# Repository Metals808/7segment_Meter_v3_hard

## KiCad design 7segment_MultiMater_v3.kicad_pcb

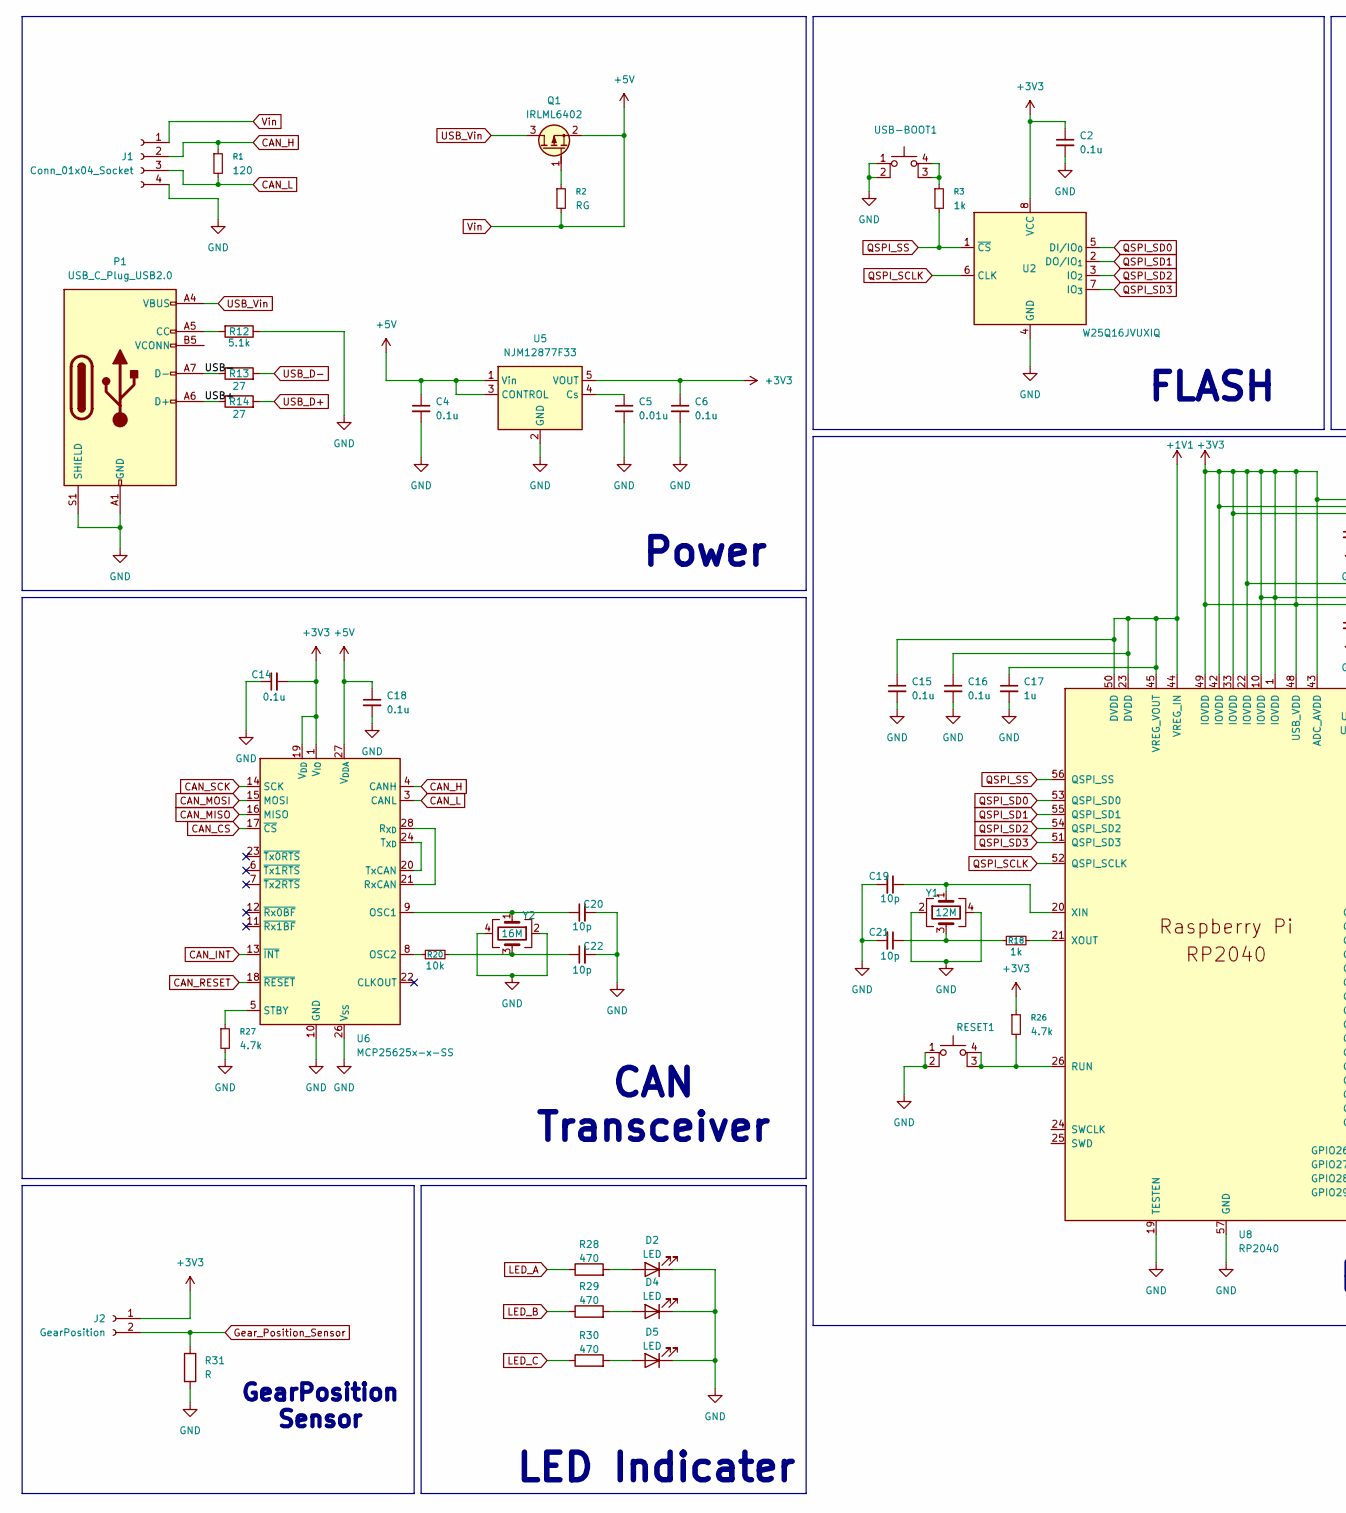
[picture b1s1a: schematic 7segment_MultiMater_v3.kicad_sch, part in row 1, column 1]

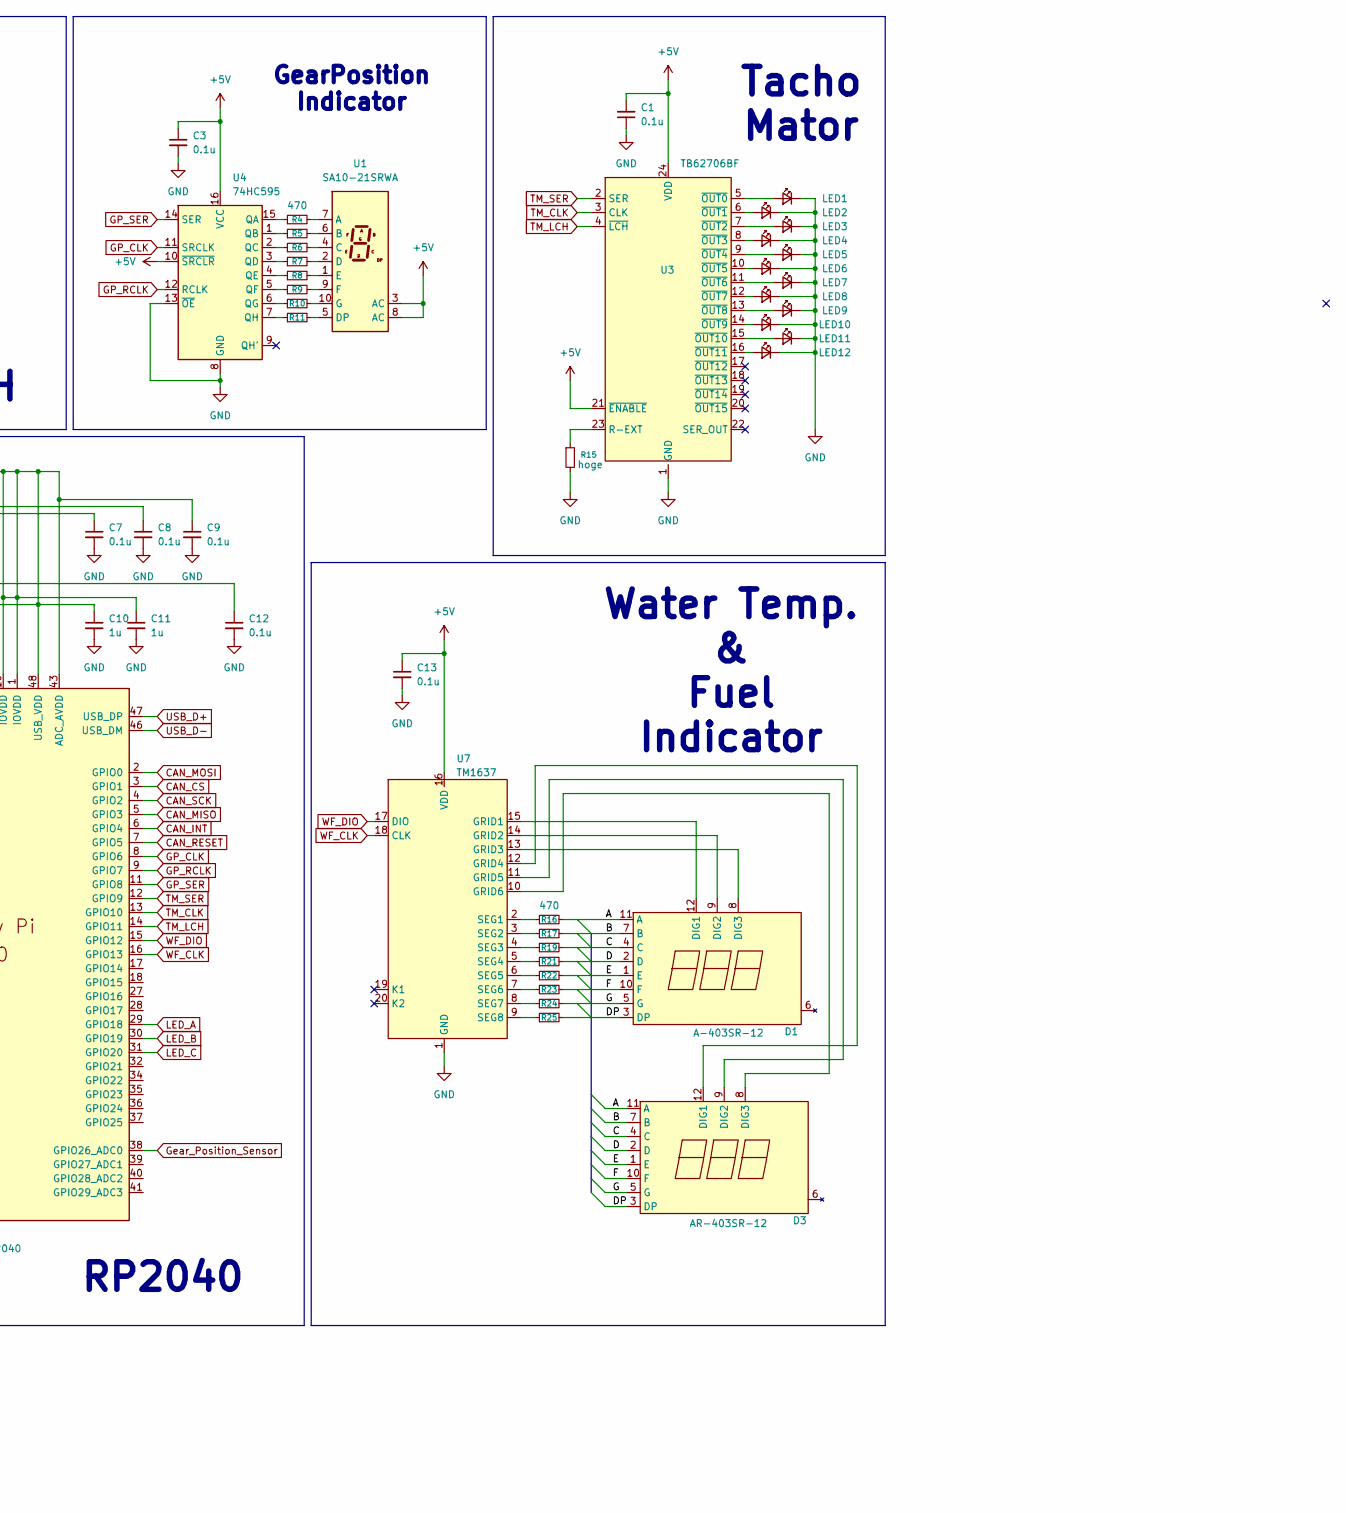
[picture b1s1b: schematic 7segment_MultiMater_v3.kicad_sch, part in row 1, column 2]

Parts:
C1, C2, C3, C4, C6, C7, C8, C9, C12, C13, C14, C15, C16, C18: 0.1u; C_0402_1005Metric
C5: 0.01u; C_0402_1005Metric
C10, C11, C17: 1u; C_0402_1005Metric
C19, C20, C21, C22: 10p; C_0402_1005Metric
D1: A-403SR-12; A403SR-12
D2, D4, D5: LED; LED_0603_1608Metric_Pad1.05x0.95mm_HandSolder
D3: AR-403SR-12; A403SR-12
J1: Conn_01x04_Socket; JST_PH_B4B-PH-K_1x04_P2.00mm_Vertical
J2: GearPosition; JST_PH_B2B-PH-K_1x02_P2.00mm_Vertical
LED1, LED2, LED3, LED4, LED5, LED6, LED7, LED8, LED9, LED10, LED11, LED12: LED_Small; LED_D3.0mm
P1: USB_C_Plug_USB2.0; USB_C_Receptacle_HCTL_HC-TYPE-C-16P-01A
Q1: IRLML6402; SOT-23
R1: 120; C_0603_1608Metric
R2: RG; R_0402_1005Metric
R3, R18: 1k; R_0402_1005Metric
R4, R5, R6, R7, R8, R9, R10, R11, R16, R17, R19, R21, R22, R23, R24, R25, R28, R29, R30: 470; R_0402_1005Metric
R12: 5.1k; R_0603_1608Metric
R13, R14: 27; R_0603_1608Metric
R15: hoge; R_0402_1005Metric
R20: 10k; R_0402_1005Metric
R26, R27: 4.7k; R_0402_1005Metric
R31: R; R_0603_1608Metric
RESET1: RESET; SKRPACE010
U1: SA10-21SRWA
U2: W25Q16JVUXIQ; Winbond_USON-8-1EP_3x2mm_P0.5mm_EP0.2x1.6mm
U3: TB62706BF; SSOP-24_3.9x8.7mm_P0.635mm
U4: 74HC595; SOP-16_4.4x10.4mm_P1.27mm
U5: NJM12877F33; SOT-23-5_HandSoldering
U6: MCP25625x-x-SS; SSOP-28_5.3x10.2mm_P0.65mm
U7: TM1637; SOP-20_7.5x12.8mm_P1.27mm
U8: RP2040; QFN-56-1EP_7x7mm_P0.4mm_EP3.2x3.2mm
USB-BOOT1: USB_BOOT_SWITCH; SKRPACE010
Y1: 12M; Crystal_SMD_3225-4Pin_3.2x2.5mm
Y2: 16M; Crystal_SMD_3225-4Pin_3.2x2.5mm

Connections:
+1V1: C15.1, C16.1, C17.1, U8.23 (DVDD), U8.44 (VREG_IN), U8.45 (VREG_VOUT), U8.50 (DVDD)
+3V3: C2.1, C6.1, C7.1, C8.1, C9.1, C10.1, C11.1, C12.1, C14.2, J2.1, R26.1, U2.8 (VCC), U5.5 (VOUT), U6.1 (V_{IO}), U6.19 (V_{DD}), U8.1 (IOVDD), U8.10 (IOVDD), U8.22 (IOVDD), U8.33 (IOVDD), U8.42 (IOVDD), U8.43 (ADC_AVDD), U8.48 (USB_VDD), U8.49 (IOVDD)
/A: D1.11 (A), D3.11 (A), R16.2
/B: D1.7 (B), D3.7 (B), R17.2
/C: D1.4 (C), D3.4 (C), R19.2
/D: D1.2 (D), D3.2 (D), R21.2
/DP: D1.3 (DP), D3.3 (DP), R25.2
/E: D1.1 (E), D3.1 (E), R22.2
/F: D1.10 (F), D3.10 (F), R23.2
/G: D1.5 (G), D3.5 (G), R24.2
/USB+: P1.A6 (D+), R14.1
/USB-: P1.A7 (D-), R13.1
CAN_CS: U6.17 (~CS), U8.3 (GPIO1)
CAN_H: J1.2, R1.1, U6.4 (CANH)
CAN_INT: U6.13 (~INT), U8.6 (GPIO4)
CAN_L: J1.3, R1.2, U6.3 (CANL)
CAN_MISO: U6.16 (MISO), U8.5 (GPIO3)
CAN_MOSI: U6.15 (MOSI), U8.2 (GPIO0)
CAN_RESET: U6.18 (~RESET), U8.7 (GPIO5)
CAN_SCK: U6.14 (SCK), U8.4 (GPIO2)
GND: C1.1, C2.2, C3.2, C4.2, C5.2, C6.2, C7.2, C8.2, C9.2, C10.2, C11.2, C12.2, C13.2, C14.1, C15.2, C16.2, C17.2, C18.2, C19.2, C20.2, C21.2, C22.2, D2.1 (K), D4.1 (K), D5.1 (K), J1.4, LED1.1 (K), LED2.1 (K), LED3.1 (K), LED4.1 (K), LED5.1 (K), LED6.1 (K), LED7.1 (K), LED8.1 (K), LED9.1 (K), LED10.1 (K), LED11.1 (K), LED12.1 (K), P1.A1 (GND), P1.A12 (GND), P1.B1 (GND), P1.B12 (GND), P1.S1 (SHIELD), R12.1, R15.2, R27.2, R31.2, RESET1.1, RESET1.2, U2.4 (GND), U3.1 (GND), U4.8 (GND), U4.13 (~OE), U5.2 (GND), U6.10 (GND), U6.26 (V_{SS}), U7.1 (GND), U8.19 (TESTEN), U8.57 (GND), USB-BOOT1.1, USB-BOOT1.2, Y1.2, Y1.4, Y2.2, Y2.4
GP_CLK: U4.11 (SRCLK), U8.8 (GPIO6)
GP_RCLK: U4.12 (RCLK), U8.9 (GPIO7)
GP_SER: U4.14 (SER), U8.11 (GPIO8)
Gear_Position_Sensor: J2.2, R31.1, U8.38 (GPIO26_ADC0)
LED_A: R28.1, U8.29 (GPIO18)
LED_B: R29.1, U8.30 (GPIO19)
LED_C: R30.1, U8.31 (GPIO20)
unnamed: C21.1, R18.1, Y1.3
unnamed: C22.1, R20.2, Y2.3
unnamed: D1.12 (DIG1), U7.15 (GRID1)
unnamed: D1.9 (DIG2), U7.14 (GRID2)
unnamed: D1.8 (DIG3), U7.13 (GRID3)
unnamed: D2.2 (A), R28.2
unnamed: D3.12 (DIG1), U7.12 (GRID4)
unnamed: D3.9 (DIG2), U7.11 (GRID5)
unnamed: D3.8 (DIG3), U7.10 (GRID6)
unnamed: D4.2 (A), R29.2
unnamed: D5.2 (A), R30.2
unnamed: LED1.2 (A), U3.5 (~OUT0)
unnamed: LED2.2 (A), U3.6 (~OUT1)
unnamed: LED3.2 (A), U3.7 (~OUT2)
unnamed: LED4.2 (A), U3.8 (~OUT3)
unnamed: LED5.2 (A), U3.9 (~OUT4)
unnamed: LED6.2 (A), U3.10 (~OUT5)
unnamed: LED7.2 (A), U3.11 (~OUT6)
unnamed: LED8.2 (A), U3.12 (~OUT7)
unnamed: LED9.2 (A), U3.13 (~OUT8)
unnamed: LED10.2 (A), U3.14 (~OUT9)
unnamed: LED11.2 (A), U3.15 (~OUT10)
unnamed: LED12.2 (A), U3.16 (~OUT11)
unnamed: P1.A5 (CC), R12.2
unnamed: Q1.1 (G), R2.1
unnamed: R26.2, RESET1.3 (K), RESET1.4 (A), U8.26 (RUN)
unnamed: R4.2, U1.7 (A)
unnamed: R5.2, U1.6 (B)
unnamed: R6.2, U1.4 (C)
unnamed: R7.2, U1.2 (D)
unnamed: R11.2, U1.5 (DP)
unnamed: R8.2, U1.1 (E)
unnamed: R9.2, U1.9 (F)
unnamed: R10.2, U1.10 (G)
unnamed: R15.1, U3.23 (R-EXT)
unnamed: R4.1, U4.15 (QA)
unnamed: R5.1, U4.1 (QB)
unnamed: R6.1, U4.2 (QC)
unnamed: R7.1, U4.3 (QD)
unnamed: R8.1, U4.4 (QE)
unnamed: R9.1, U4.5 (QF)
unnamed: R10.1, U4.6 (QG)
unnamed: R11.1, U4.7 (QH)
unnamed: C5.1, U5.4 (Cs)
unnamed: C20.1, U6.9 (OSC1), Y2.1
unnamed: R20.1, U6.8 (OSC2)
unnamed: U6.21 (RxCAN), U6.28 (R_{XD})
unnamed: R27.1, U6.5 (STBY)
unnamed: U6.20 (TxCAN), U6.24 (T_{XD})
unnamed: R16.1, U7.2 (SEG1)
unnamed: R17.1, U7.3 (SEG2)
unnamed: R19.1, U7.4 (SEG3)
unnamed: R21.1, U7.5 (SEG4)
unnamed: R22.1, U7.6 (SEG5)
unnamed: R23.1, U7.7 (SEG6)
unnamed: R24.1, U7.8 (SEG7)
unnamed: R25.1, U7.9 (SEG8)
unnamed: C19.1, U8.20 (XIN), Y1.1
unnamed: R18.2, U8.21 (XOUT)
unnamed: R3.1, USB-BOOT1.3 (K), USB-BOOT1.4 (A)
QSPI_SCLK: U2.6 (CLK), U8.52 (QSPI_SCLK)
QSPI_SD0: U2.5 (DI/IO_{0}), U8.53 (QSPI_SD0)
QSPI_SD1: U2.2 (DO/IO_{1}), U8.55 (QSPI_SD1)
QSPI_SD2: U2.3 (IO_{2}), U8.54 (QSPI_SD2)
QSPI_SD3: U2.7 (IO_{3}), U8.51 (QSPI_SD3)
QSPI_SS: R3.2, U2.1 (~CS), U8.56 (QSPI_SS)
TM_CLK: U3.3 (CLK), U8.13 (GPIO10)
TM_LCH: U3.4 (~LCH), U8.14 (GPIO11)
TM_SER: U3.2 (SER), U8.12 (GPIO9)
USB_D+: R14.2, U8.47 (USB_DP)
USB_D-: R13.2, U8.46 (USB_DM)
USB_Vin: P1.A4 (VBUS), P1.A9 (VBUS), P1.B4 (VBUS), P1.B9 (VBUS), Q1.3 (D)
Vin: C1.2, C3.1, C4.1, C13.1, C18.1, J1.1, Q1.2 (S), R2.2, U1.3 (AC), U1.8 (AC), U3.21 (~ENABLE), U3.24 (VDD), U4.10 (~SRCLR), U4.16 (VCC), U5.1 (Vin), U5.3 (CONTROL), U6.27 (V_{DDA}), U7.16 (VDD)
WF_CLK: U7.18 (CLK), U8.16 (GPIO13)
WF_DIO: U7.17 (DIO), U8.15 (GPIO12)

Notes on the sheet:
FLASH
Water Temp. & Fuel Indicator
GearPosition Indicator
Power
CAN Transceiver
RP2040
Tacho Mator
LED Indicater
GearPosition Sensor

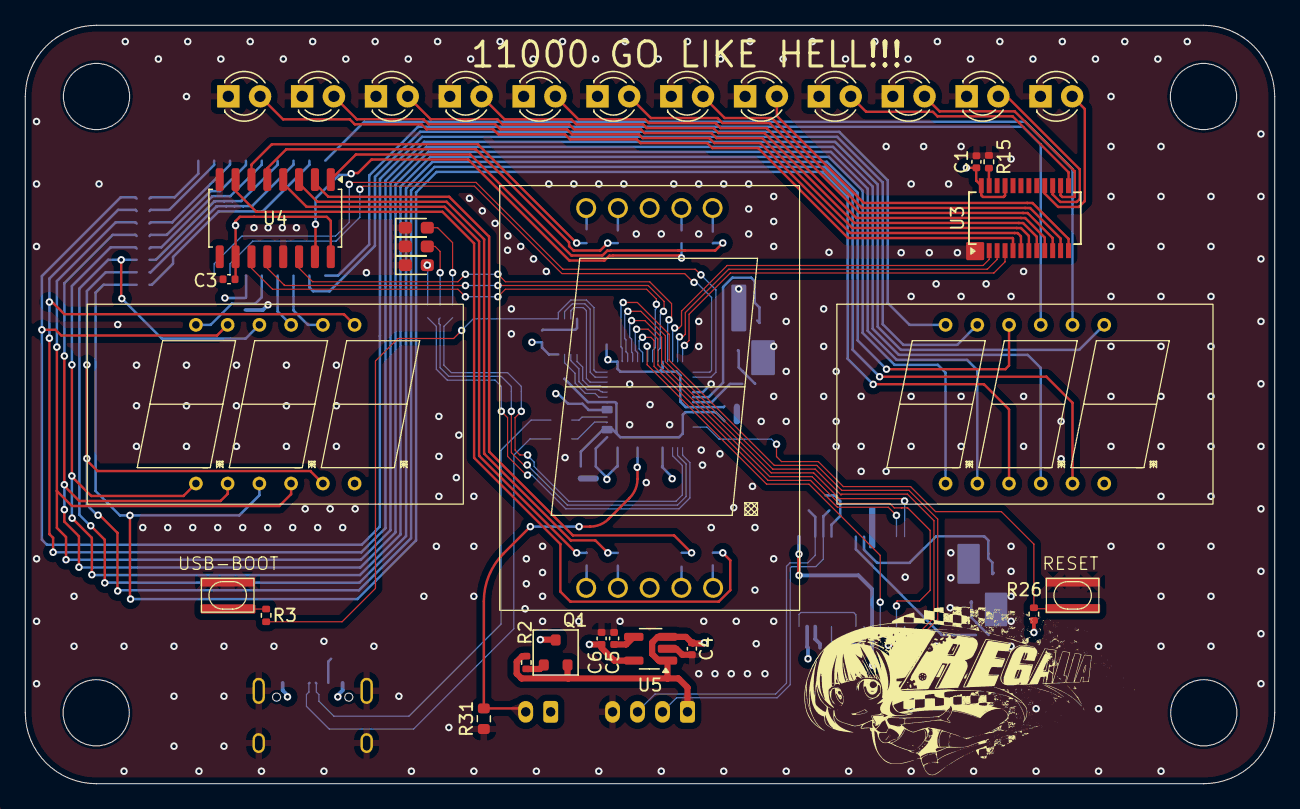
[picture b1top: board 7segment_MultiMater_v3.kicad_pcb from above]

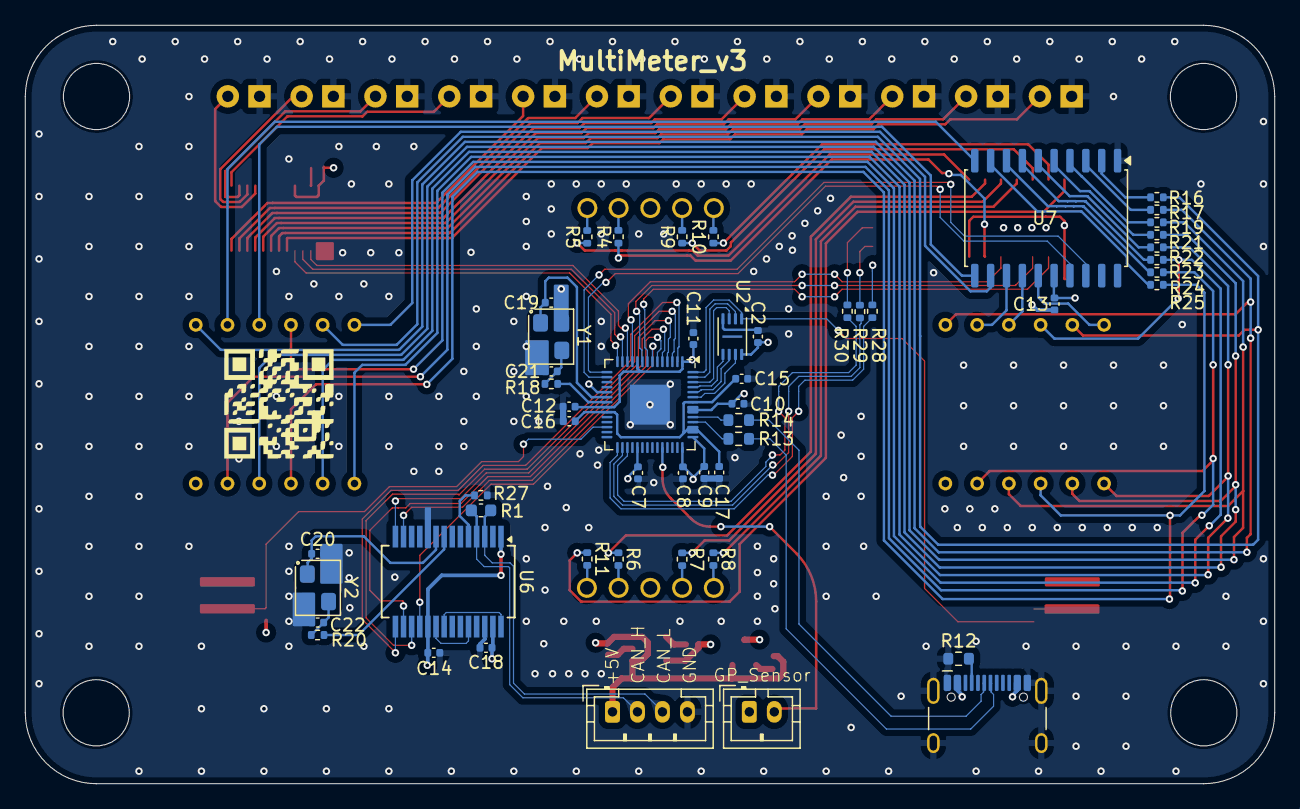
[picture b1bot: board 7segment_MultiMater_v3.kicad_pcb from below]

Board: 4 copper layers, 100.0 x 60.7 mm, 86 parts (52 on the bottom side), 103 nets.

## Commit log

2025-11-14 first comit
2025-11-15 シルク追加
2025-11-15 コメント追加
